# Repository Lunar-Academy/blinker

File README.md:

# blinker
Simple LED Blinker with LM555 for various purposes

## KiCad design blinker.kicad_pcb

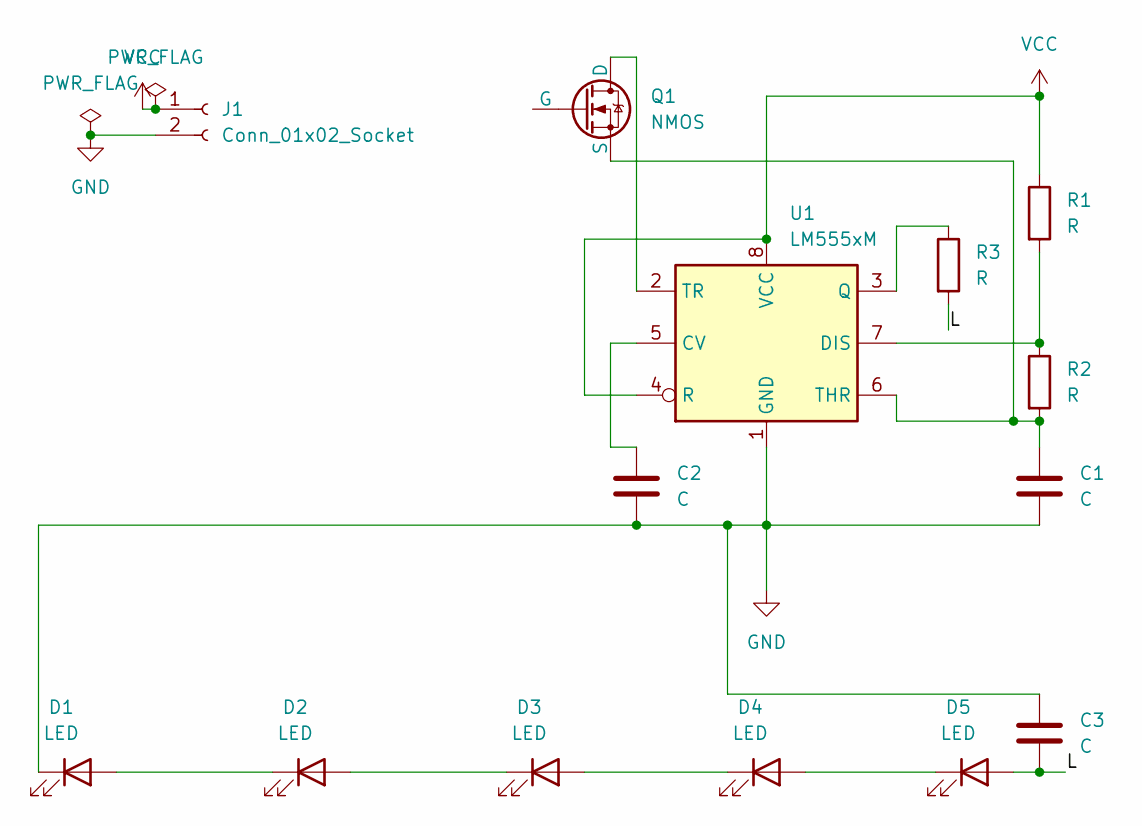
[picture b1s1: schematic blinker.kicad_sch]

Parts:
C1, C2, C3: C; C_0201_0603Metric
D1, D2, D3, D4, D5: LED; LED_1W_3W_R8
J1: Conn_01x02_Socket; AMASS_XT60-F_1x02_P7.20mm_Vertical
Q1: NMOS; TO-92Flat
R1, R2, R3: R; R_LDR_5.0x4.1mm_P3mm_Vertical
U1: LM555xM; SOIC-8_3.9x4.9mm_P1.27mm

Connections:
/L: C3.2, D5.2 (A), R3.2
GND: C1.2, C2.2, C3.1, D1.1 (K), J1.2, U1.1 (GND)
unnamed: D1.2 (A), D2.1 (K)
unnamed: D2.2 (A), D3.1 (K)
unnamed: D3.2 (A), D4.1 (K)
unnamed: D4.2 (A), D5.1 (K)
unnamed: Q1.1 (D), U1.2 (TR)
unnamed: C1.1, Q1.3 (S), R2.2, U1.6 (THR)
unnamed: C2.1, U1.5 (CV)
unnamed: R1.2, R2.1, U1.7 (DIS)
unnamed: R3.1, U1.3 (Q)
VCC: J1.1, R1.1, U1.4 (R), U1.8 (VCC)

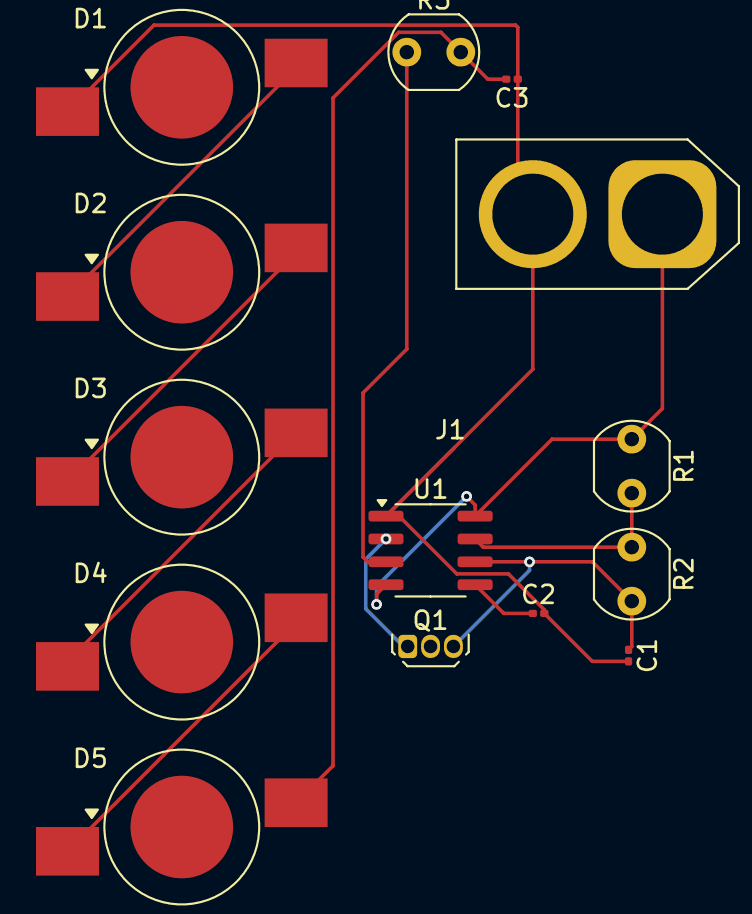
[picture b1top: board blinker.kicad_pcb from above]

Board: 2 copper layers, 14 parts (0 on the bottom side), 12 nets.

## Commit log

2025-09-06 Add image to README for enhanced documentation
    Added an image to the README for better visualization.
